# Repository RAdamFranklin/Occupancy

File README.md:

# Occupancy
2015-2016 senior design. 

Occupancy is a system of sensors that can be spread across a building and be analyzed, in our case we are designing it for a college library. These sensory units will be used in order to establish the number of people in each area, and the amount of time they spend in each area. This information can then be used in order to make the library more convenient for students. 

#CO2 Grid-EYE
This code is used on a Tiva Launchpad with a CO2 sensor and a Grid-EYE. The CO2 sensor picks up the amount of CO2 in each area which can be used to establish the amount of people within the area and we can establish the air quality of it. The Grid-EYE is an 8x8 grid of tempurature, and from a top down veiw we can use this in order to establish the number of people in a ten foot area. 

#Occupancy-Testing
Occupancy test v1.1 is the first iteration of having the system 'working.' The central unit sends a remote at command request via it's xbee to the sensor nodes xbee. This raises a pin on the xbee which activates a pin interrupt on the launchpad, which leads to the launchpad reading the data from the sensors, then sending this data back over the xbee to the central unit. See RPi serial format for packet structure

#PCB 
The .brd and .sch files were created using Eagle CS for the Occupancy project. These files will be converted into Gerber files to be sent to a professional fabricator. 

#Python Sqlite Database
python sqlite database.py is written in python and uses sqlite3 to create a database with a single table with a number of columns capable of storing all the sensor data. 

#Reading Serial and Writing to Sqlite Database
SerialIOdatabase.py is written in python and request data from a sensor node reads in the serial input, converts it from hexadecimal to decimal and then stores it in the sqlite database.

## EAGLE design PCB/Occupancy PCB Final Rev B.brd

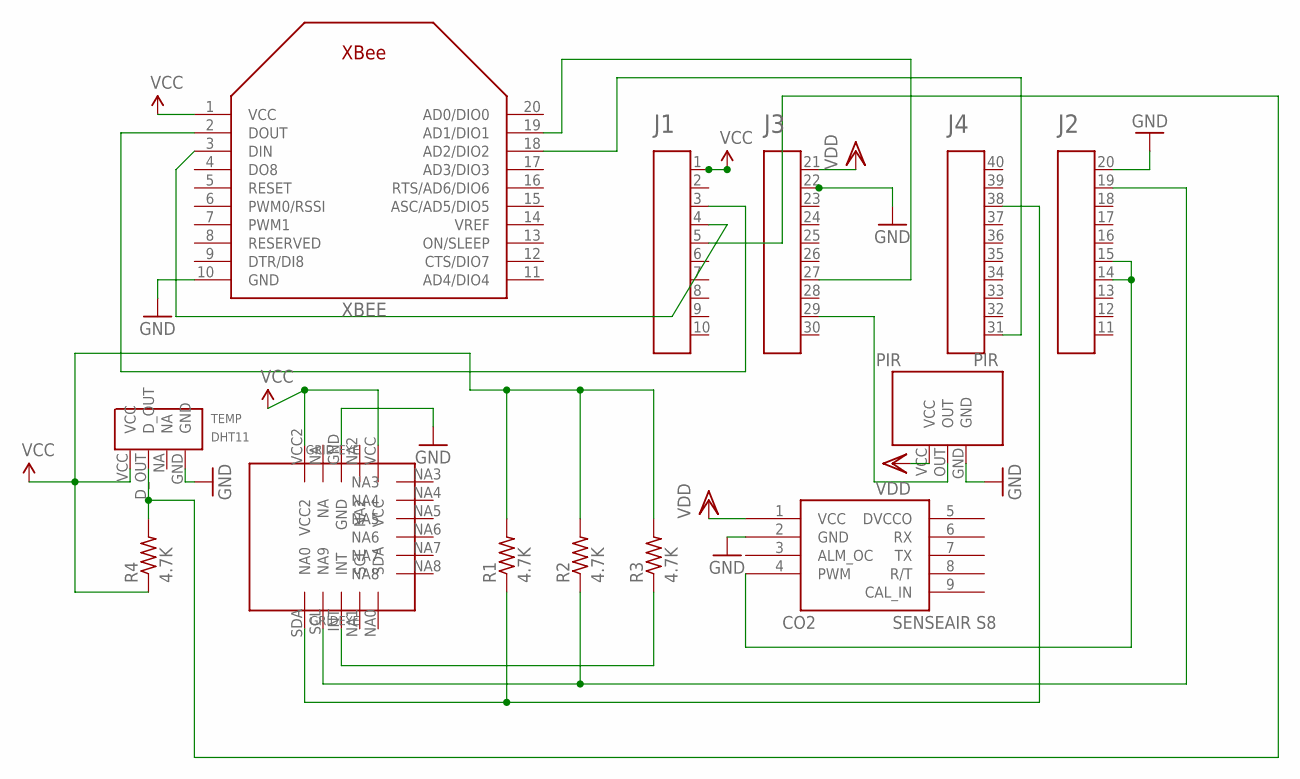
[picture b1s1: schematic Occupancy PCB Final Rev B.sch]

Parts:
CO2: SENSEAIR-S8-DIP
GRIDEYE: GRID-EYE-DIP
LAUNCHPAD: HEADER4X10-BOOSTERPACK; 4X10-BOOSTERPACK
PIR: PIR-DIP
R1, R2, R3, R4: 4.7K; R0805
TEMP: DHT11-DIP
XBEE: XBEE

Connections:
GND: CO2.2 (GND), GRIDEYE.GND, LAUNCHPAD.20, LAUNCHPAD.22, PIR.GND, TEMP.GND, XBEE.10 (GND)
unnamed: LAUNCHPAD.31, XBEE.18 (AD2/DIO2)
unnamed: GRIDEYE.SDA (NA0), LAUNCHPAD.38, R1.1
unnamed: CO2.4 (PWM), LAUNCHPAD.14, LAUNCHPAD.15
unnamed: LAUNCHPAD.3, XBEE.2 (DOUT)
unnamed: LAUNCHPAD.4, XBEE.3 (DIN)
unnamed: GRIDEYE.SCL (NA9), LAUNCHPAD.19, R2.1
unnamed: GRIDEYE.INT, R3.1
unnamed: LAUNCHPAD.5, R4.2, TEMP.D_OUT
unnamed: LAUNCHPAD.27, XBEE.19 (AD1/DIO1)
unnamed: LAUNCHPAD.29, PIR.OUT
VCC: GRIDEYE.VCC, GRIDEYE.VCC2, LAUNCHPAD.1, R1.2, R2.2, R3.2, R4.1, TEMP.VCC, XBEE.1 (VCC)
VDD: CO2.1 (VCC), LAUNCHPAD.21, PIR.VCC

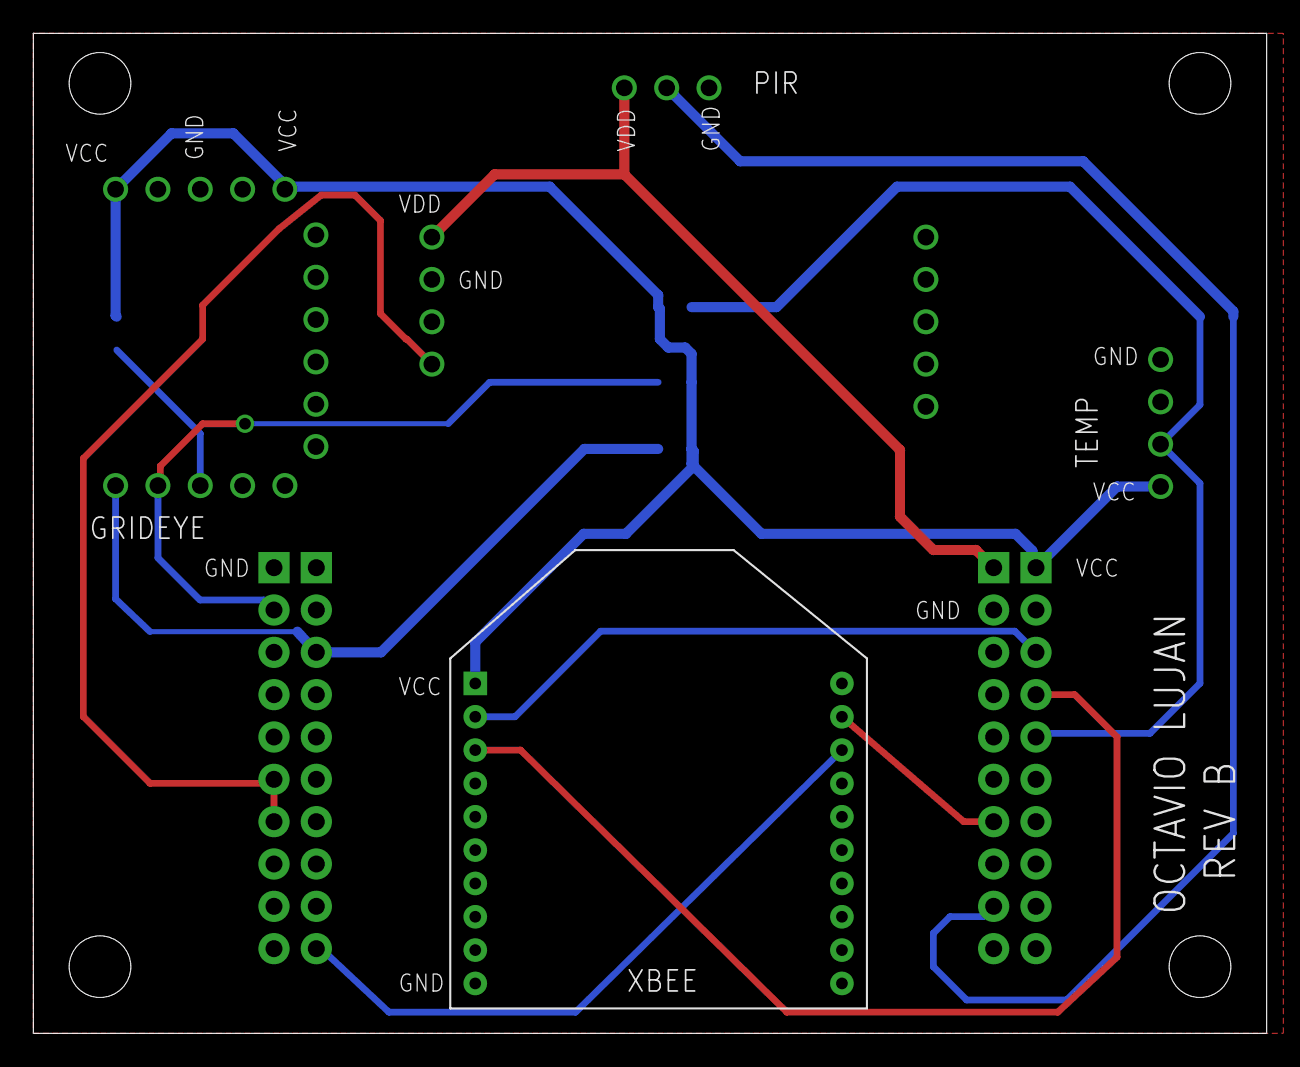
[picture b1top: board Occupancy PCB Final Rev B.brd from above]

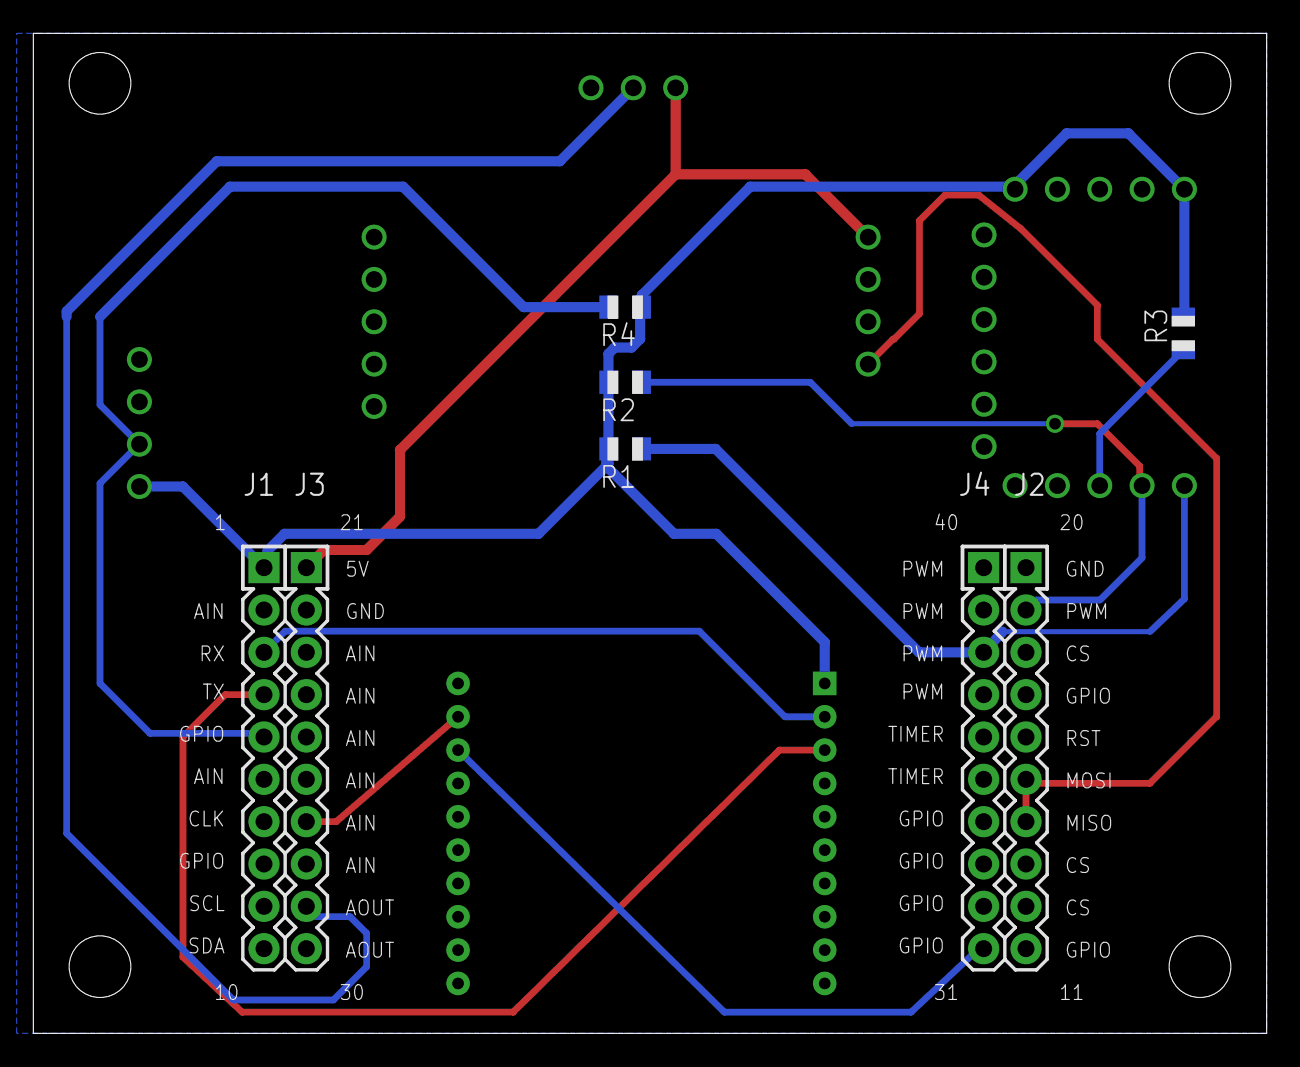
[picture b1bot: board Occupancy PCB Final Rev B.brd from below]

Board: 2 copper layers, 74.0 x 60.0 mm, 10 parts (5 on the bottom side), 13 nets.

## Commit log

2016-04-16 Added files via upload
    Generates a sqlite database
2016-04-18 Placing Serial Data in the sqlite database
2016-04-18 Create sqlite database
2016-04-18 Ovie's final edit to pins
2016-04-28 Reads serial and places data in database

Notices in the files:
parts and their libraries:
SparkFun-Aesthetics: Licensing: Creative Commons ShareAlike 4.0 International - https://creativecommons.org/licenses/by-sa/4.0
